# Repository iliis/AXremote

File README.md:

NOTE on AX5043 / AX8052F143 support
===================================

If you need help with an AX5043 based project please contact AxsemSupport@onsemi.com first ;)

AXremote
========

Wireless remote for XBMC and other things.

TODO
====

Software
--------
- use deepsleep for radio instead of powerdown
- put mcu into sleep, disable all timers

Hardware
--------
- add GND and VCC vias to PCB (2.57mm pinheader) for easy current measurement
- use DSWAKE and put chip into deepsleep

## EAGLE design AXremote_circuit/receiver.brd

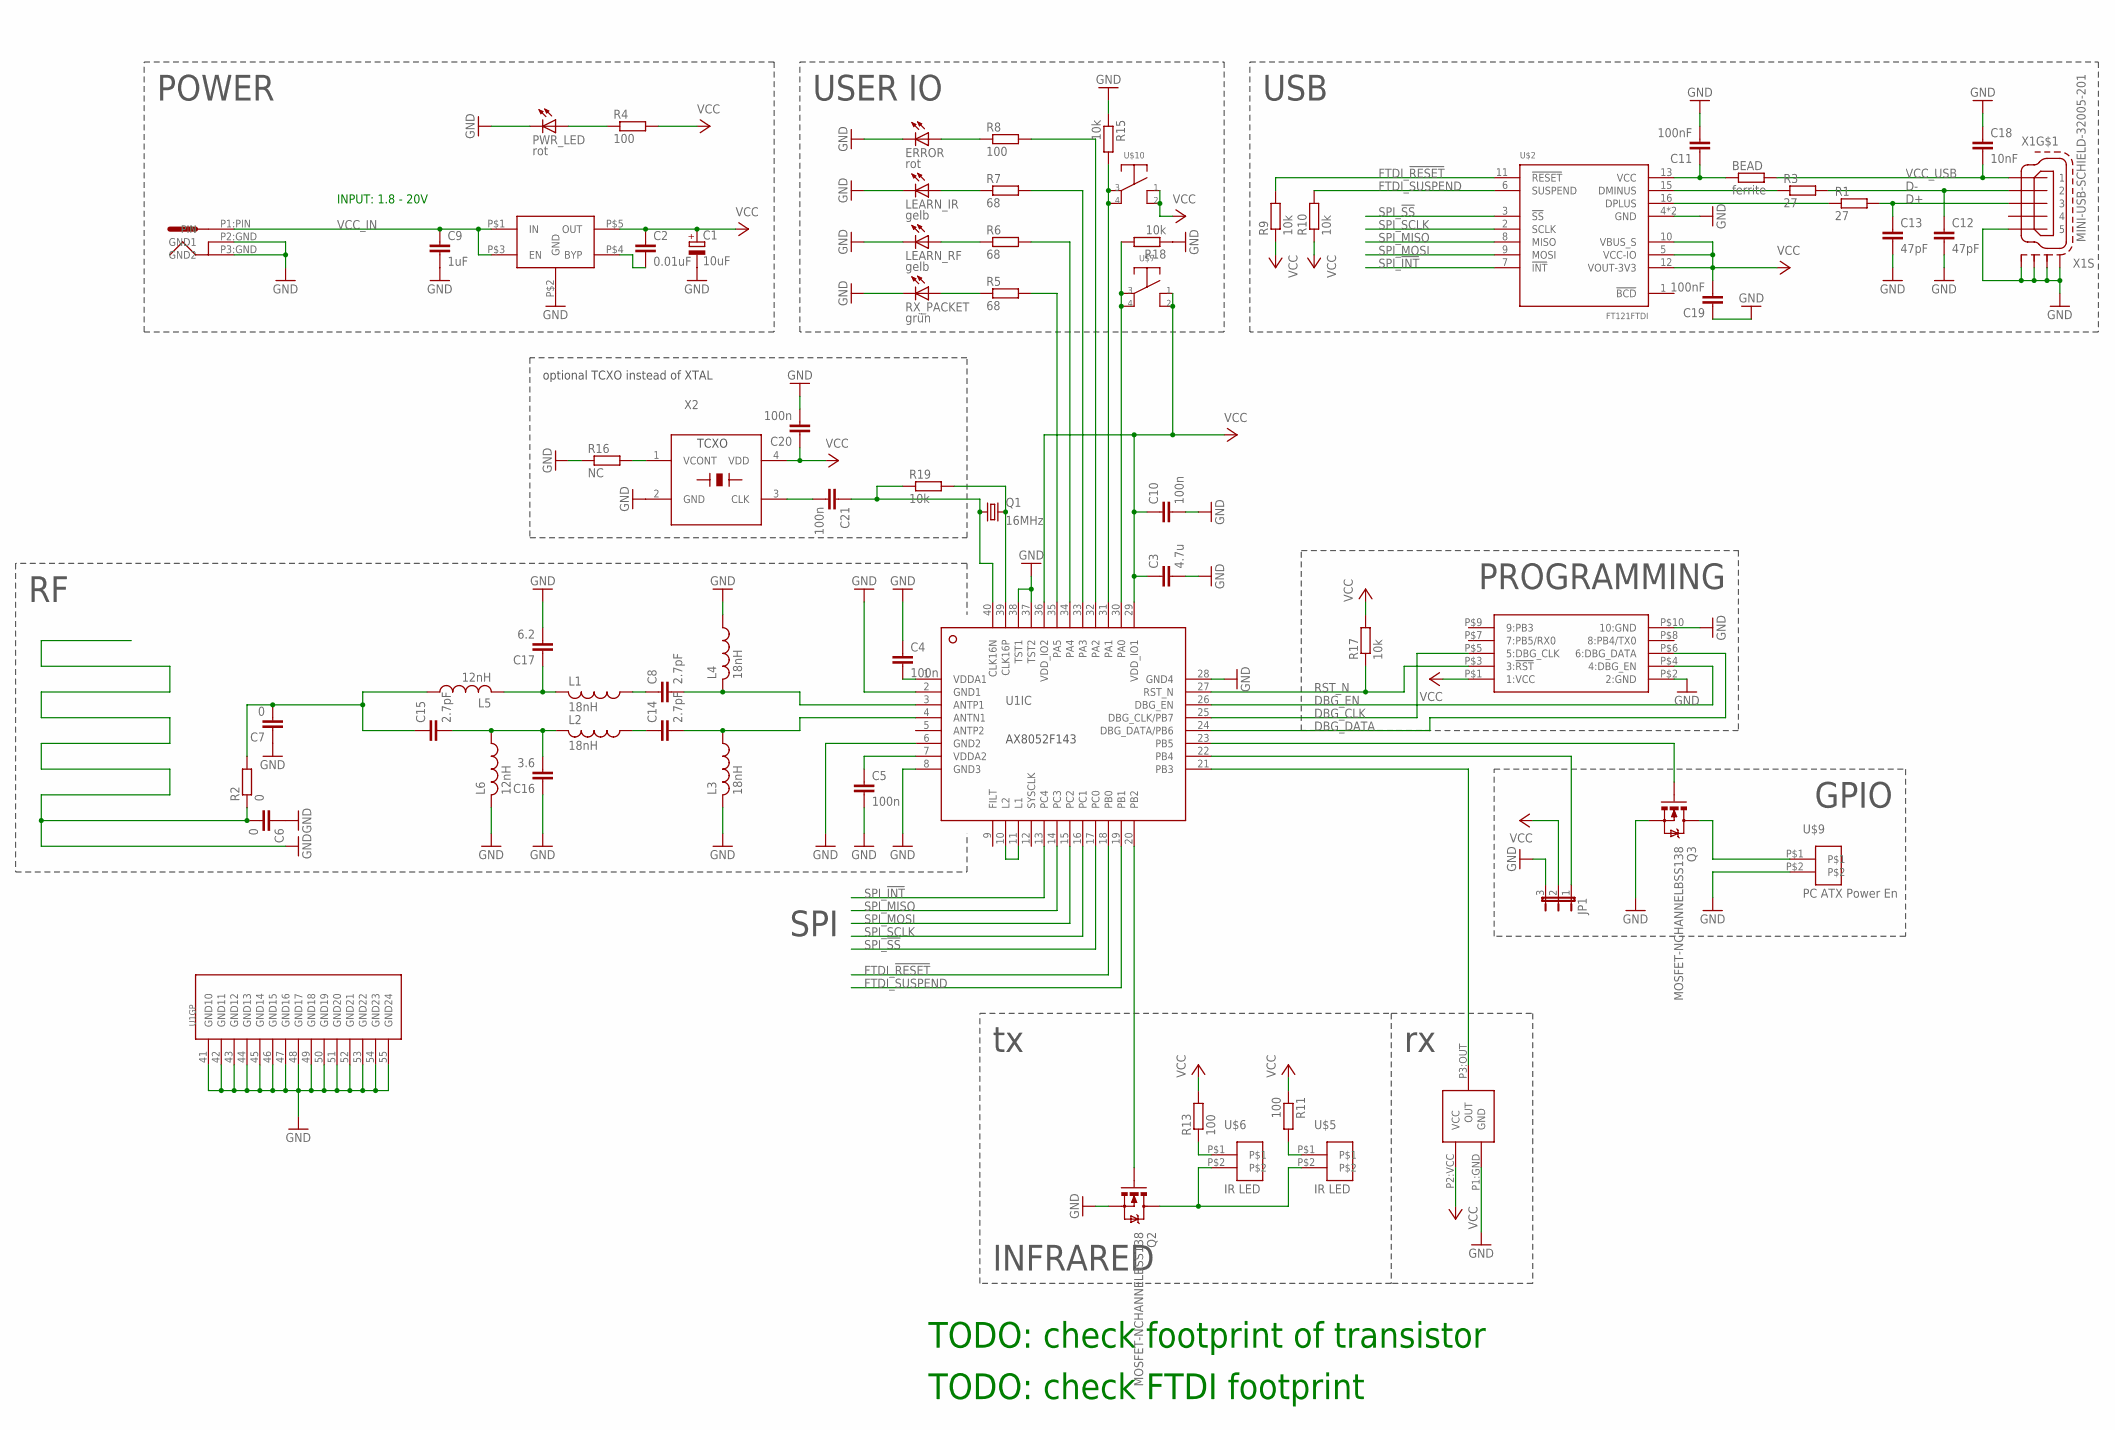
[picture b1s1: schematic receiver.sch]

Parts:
BEAD: ferrite; R0603
C1: 10uF; 153CLV-0405
C2: 0.01uF; C0603
C3: 4.7u; C0805
C4, C5, C10, C20, C21: 100n; C0603
C6, C7: 0; C0603
C8, C14, C15: 2.7pF; C0603
C9: 1uF; C0805K
C11, C19: 100nF; C0603K
C12, C13: 47pF; C0603K
C16: 3.6; C0603
C17: 6.2; C0603
C18: 10nF; C0603K
ERROR: rot; CHIPLED_1206
JP1: JP2E; JP2
L1, L2, L3, L4: 18nH; C0603
L5, L6: 12nH; C0603
LEARN_IR: gelb; CHIPLED_1206
LEARN_RF: gelb; CHIPLED_1206
PWR_LED: rot; CHIPLED_1206
Q1: 16MHz; SM49
Q2, Q3: MOSFET-NCHANNELBSS138; SOT23
R1, R3: 27; R0603
R2: 0; R0603
R4, R8, R11, R13: 100; R0603
R5, R6, R7: 68; R0603
R9, R10, R15, R17, R18, R19: 10k; R0603
R16: NC; R0603
RX_PACKET: grün; CHIPLED_1206
U1: AX8052F143HS; QFN40-H
U$1: LT1761; TSOT-23
U$2: FT121FTDI; TSSOP16-FTDI
U$3: 2X5PIN-CONNECTOR; 2X5PIN-CONNECTOR-SMD
U$4: POWER_JACK; POWER_JACK_3.4/1
U$5, U$6: IR LED; 2PIN_PINHEADER
U$7, U$10: SWITCHSMD; TACTILE_SWITCH_FSM2JSMA
U$8: IR_RECEIVER; TSOP1738_IR_RECV
U$9: PC ATX Power En; 2PIN_PINHEADER
X1: MINI-USB-SCHIELD-32005-201; 32005-201
X2: TCXO3225; X3225

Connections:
D+: C13.1, R1.2, X1.3
D-: C12.1, R3.2, X1.2
DBG_CLK: U1.25 (DBG_CLK/PB7), U$3.P$5 (5:DBG_CLK)
DBG_DATA: U1.24 (DBG_DATA/PB6), U$3.P$6 (6:DBG_DATA)
DBG_EN: U1.26 (DBG_EN), U$3.P$4 (4:DBG_EN)
FTDI_!RESET: R9.2, U1.18 (PB0), U$2.11 (!RESET)
FTDI_SUSPEND: R10.2, U1.19 (PB1), U$2.6 (SUSPEND)
GND: C1.-, C3.2, C4.1, C5.2, C6.1, C6.2, C7.1, C9.2, C10.2, C11.2, C12.2, C13.2, C16.1, C17.2, C18.1, C19.1, C20.2, ERROR.C, JP1.3, L3.2, L4.1, L6.2, LEARN_IR.C, LEARN_RF.C, PWR_LED.C, Q2.2 (S), Q3.2 (S), R2.1, R15.1, R16.1, R18.1, RX_PACKET.C, U1.2 (GND1), U1.6 (GND2), U1.8 (GND3), U1.28 (GND4), U1.37 (TST2), U1.38 (TST1), U1.41 (GND10), U1.42 (GND11), U1.43 (GND12), U1.44 (GND13), U1.45 (GND14), U1.46 (GND15), U1.47 (GND16), U1.48 (GND17), U1.49 (GND18), U1.50 (GND19), U1.51 (GND20), U1.52 (GND21), U1.53 (GND22), U1.54 (GND23), U1.55 (GND24), U$1.P$2 (GND), U$2.4 (GND), U$2.14 (GND), U$3.P$2 (2:GND), U$3.P$10 (10:GND), U$4.P2:GND (GND1), U$4.P3:GND (GND2), U$8.P1:GND (GND), U$9.P$2, X1.5, X1.M1 (S1), X1.M2 (S2), X1.M3 (S3), X1.M4 (S4), X2.2 (GND)
unnamed: U1.10 (L2), U1.11 (L1)
unnamed: R1.1, U$2.16 (DPLUS)
unnamed: C4.2, U1.1 (VDDA1)
unnamed: C2.2, U$1.P$4 (BYP)
unnamed: R3.1, U$2.15 (DMINUS)
unnamed: C5.1, U1.7 (VDDA2)
unnamed: C8.2, L4.2, U1.3 (ANTP1)
unnamed: C14.2, L3.1, U1.4 (ANTN1)
unnamed: C8.1, L1.1
unnamed: C14.1, L2.1
unnamed: BEAD.1, C11.1, U$2.13 (VCC)
unnamed: C17.1, L1.2, L5.2
unnamed: C15.2, C16.2, L2.2, L6.1
unnamed: Q1.2, R19.2, U1.39 (CLK16P)
unnamed: C21.1, Q1.1, R19.1, U1.40 (CLK16N)
unnamed: JP1.1, U1.22 (PB4)
unnamed: R15.2, U1.31 (PA1), U$10.P3, U$10.P4
unnamed: PWR_LED.A, R4.1
unnamed: R16.2, X2.1 (VCONT)
unnamed: C7.2, C15.1, L5.1, R2.2
unnamed: U1.21 (PB3), U$8.P3:OUT (OUT)
unnamed: C21.2, X2.3 (CLK)
unnamed: R5.1, RX_PACKET.A
unnamed: R5.2, U1.35 (PA5)
unnamed: R18.2, U1.30 (PA0), U$7.P3, U$7.P4
unnamed: LEARN_RF.A, R6.1
unnamed: LEARN_IR.A, R7.1
unnamed: ERROR.A, R8.1
unnamed: R6.2, U1.34 (PA4)
unnamed: R7.2, U1.33 (PA3)
unnamed: R8.2, U1.32 (PA2)
unnamed: R11.2, U$5.P$1
unnamed: R13.1, U$6.P$1
unnamed: Q2.3 (D), U$5.P$2, U$6.P$2
unnamed: Q2.1 (G), U1.20 (PB2)
unnamed: Q3.1 (G), U1.23 (PB5)
unnamed: Q3.3 (D), U$9.P$1
RST_N: R17.1, U1.27 (RST_N), U$3.P$3 (3:!RST)
SPI_!INT: U1.13 (PC4), U$2.7 (!INT)
SPI_!SS: U1.17 (PC0), U$2.3 (!SS)
SPI_MISO: U1.14 (PC3), U$2.8 (MISO)
SPI_MOSI: U1.15 (PC2), U$2.9 (MOSI)
SPI_SCLK: U1.16 (PC1), U$2.2 (SCLK)
VCC: C1.+, C2.1, C3.1, C10.1, C19.2, C20.1, JP1.2, R4.2, R9.1, R10.1, R11.1, R13.2, R17.2, U1.29 (VDD_IO1), U1.36 (VDD_IO2), U$1.P$5 (OUT), U$2.5 (VCC-IO), U$2.10 (VBUS_S), U$2.12 (VOUT-3V3), U$3.P$1 (1:VCC), U$7.P1, U$7.P2, U$8.P2:VCC (VCC), U$10.P1, U$10.P2, X2.4 (VDD)
VCC_IN: C9.1, U$1.P$1 (IN), U$1.P$3 (EN), U$4.P1:PIN (PIN)
VCC_USB: BEAD.2, C18.2, X1.1

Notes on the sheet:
INPUT: 1.8 - 20V
TODO: check footprint of transistor
optional TCXO instead of XTAL
POWER
USER IO
USB
INFRARED
GPIO
PROGRAMMING
SPI
TODO: check FTDI footprint

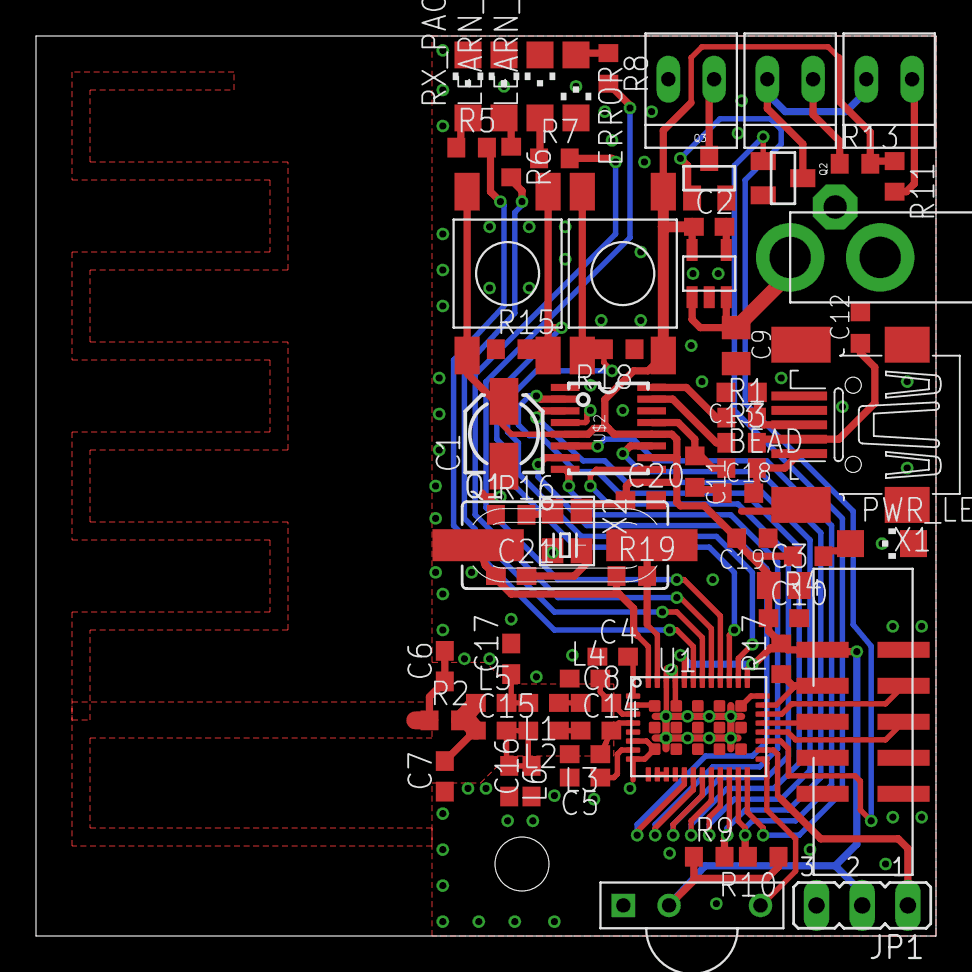
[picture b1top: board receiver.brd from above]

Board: 2 copper layers, 50.0 x 50.0 mm, 68 parts (1 on the bottom side), 54 nets.

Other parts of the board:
U$11: APERTURE_LOGO_BLACK

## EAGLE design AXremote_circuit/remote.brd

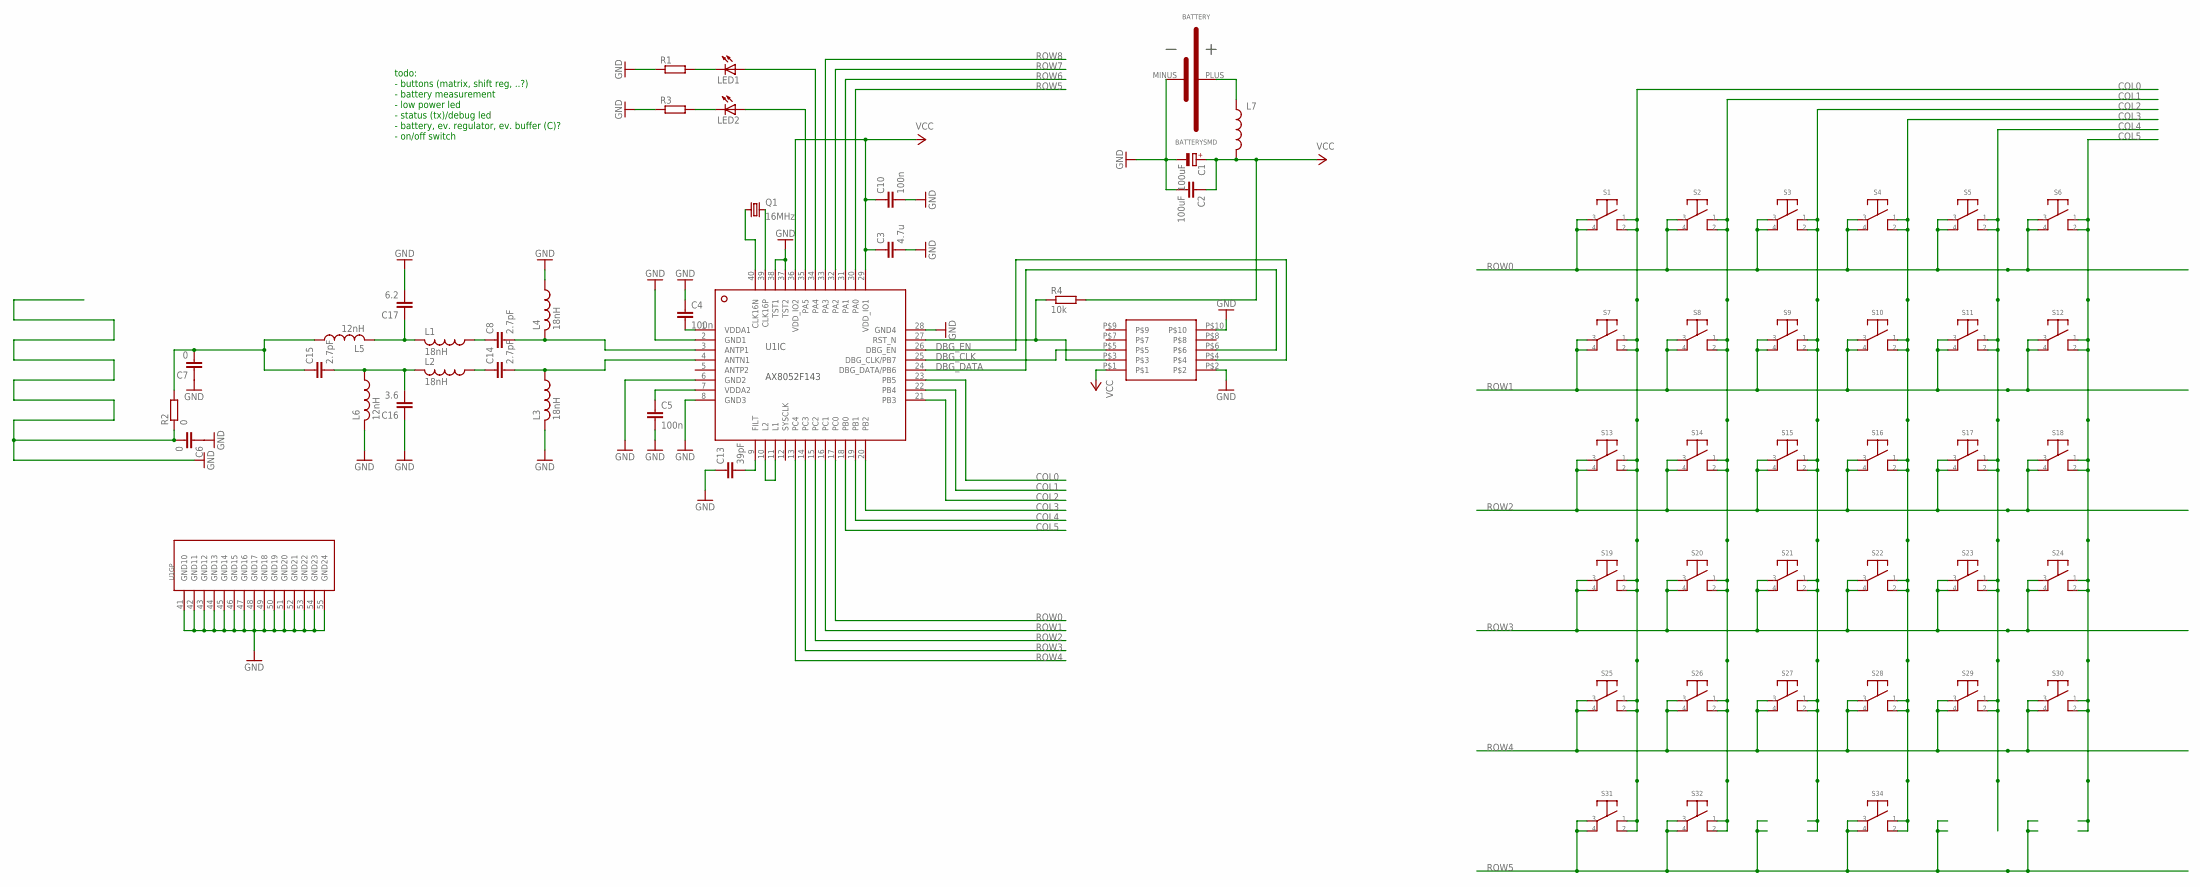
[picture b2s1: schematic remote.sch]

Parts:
BATTERY: BATTERYSMD; CR2032-SMD
C1: 100uF; PANASONIC_E
C2: 100uF; C1206K
C3: 4.7u; C0805
C4, C5, C10: 100n; C0603
C6, C7: 0; C0805
C8, C14, C15: 2.7pF; C0805
C13: 39pF; C0805
C16: 3.6; C0805
C17: 6.2; C0805
L1, L2, L3, L4: 18nH; C0603
L5, L6: 12nH; C0603
L7: INDUCTORNPI75; NPI75C
LED1, LED2: LEDCHIPLED_1206; CHIPLED_1206
Q1: 16MHz; SM49
R1, R3: R-EU_R0603; R0603
R2: 0; R0603
R4: 10k; R0603
S1, S2, S3, S4, S5, S6, S7, S8, S9, S10, S11, S12, S13, S14, S15, S16, S17, S18, S19, S20, S21, S22, S23, S24, S25, S26, S27, S28, S29, S30, S31, S32, S34: SWITCHSMD; TACTILE_SWITCH_FSM2JSMA
U1: AX8052F143HS; QFN40-H
U$2: 2X5PIN-CONNECTOR; 2X5PIN-CONNECTOR-SMD

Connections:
COL0: S1.P1, S1.P2, S7.P1, S7.P2, S13.P1, S13.P2, S19.P1, S19.P2, S25.P1, S25.P2, S31.P1, S31.P2, U1.23 (PB5)
COL1: S2.P1, S2.P2, S8.P1, S8.P2, S14.P1, S14.P2, S20.P1, S20.P2, S26.P1, S26.P2, S32.P1, S32.P2, U1.22 (PB4)
COL2: S3.P1, S3.P2, S9.P1, S9.P2, S15.P1, S15.P2, S21.P1, S21.P2, S27.P1, S27.P2, U1.21 (PB3)
COL3: S4.P1, S4.P2, S10.P1, S10.P2, S16.P1, S16.P2, S22.P1, S22.P2, S28.P1, S28.P2, S34.P1, S34.P2, U1.20 (PB2)
COL4: S5.P1, S5.P2, S11.P1, S11.P2, S17.P1, S17.P2, S23.P1, S23.P2, S29.P1, S29.P2, U1.19 (PB1)
COL5: S6.P1, S6.P2, S12.P1, S12.P2, S18.P1, S18.P2, S24.P1, S24.P2, S30.P1, S30.P2, U1.18 (PB0)
DBG_CLK: U1.25 (DBG_CLK/PB7), U$2.P$5
DBG_DATA: U1.24 (DBG_DATA/PB6), U$2.P$6
DBG_EN: U1.26 (DBG_EN), U$2.P$4
GND: BATTERY.MINUS, C1.-, C2.2, C3.2, C4.1, C5.2, C6.1, C6.2, C7.1, C10.2, C13.1, C16.1, C17.2, L3.2, L4.1, L6.2, R1.1, R2.1, R3.1, U1.2 (GND1), U1.6 (GND2), U1.8 (GND3), U1.28 (GND4), U1.37 (TST2), U1.38 (TST1), U1.41 (GND10), U1.42 (GND11), U1.43 (GND12), U1.44 (GND13), U1.45 (GND14), U1.46 (GND15), U1.47 (GND16), U1.48 (GND17), U1.49 (GND18), U1.50 (GND19), U1.51 (GND20), U1.52 (GND21), U1.53 (GND22), U1.54 (GND23), U1.55 (GND24), U$2.P$2, U$2.P$10
unnamed: U1.10 (L2), U1.11 (L1)
unnamed: C13.2, U1.9 (FILT)
unnamed: C4.2, U1.1 (VDDA1)
unnamed: LED1.A, U1.34 (PA4)
unnamed: R4.1, U1.27 (RST_N), U$2.P$3
unnamed: C5.1, U1.7 (VDDA2)
unnamed: C8.2, L4.2, U1.3 (ANTP1)
unnamed: C14.2, L3.1, U1.4 (ANTN1)
unnamed: C8.1, L1.1
unnamed: C14.1, L2.1
unnamed: LED2.A, U1.35 (PA5)
unnamed: C17.1, L1.2, L5.2
unnamed: C15.2, C16.2, L2.2, L6.1
unnamed: Q1.2, U1.39 (CLK16P)
unnamed: Q1.1, U1.40 (CLK16N)
unnamed: LED2.C, R3.2
unnamed: LED1.C, R1.2
unnamed: BATTERY.PLUS, L7.1
unnamed: C7.2, C15.1, L5.1, R2.2
ROW0: S1.P3, S1.P4, S2.P3, S2.P4, S3.P3, S3.P4, S4.P3, S4.P4, S5.P3, S5.P4, S6.P3, S6.P4, U1.17 (PC0)
ROW1: S7.P3, S7.P4, S8.P3, S8.P4, S9.P3, S9.P4, S10.P3, S10.P4, S11.P3, S11.P4, S12.P3, S12.P4, U1.16 (PC1)
ROW2: S13.P3, S13.P4, S14.P3, S14.P4, S15.P3, S15.P4, S16.P3, S16.P4, S17.P3, S17.P4, S18.P3, S18.P4, U1.15 (PC2)
ROW3: S19.P3, S19.P4, S20.P3, S20.P4, S21.P3, S21.P4, S22.P3, S22.P4, S23.P3, S23.P4, S24.P3, S24.P4, U1.14 (PC3)
ROW4: S25.P3, S25.P4, S26.P3, S26.P4, S27.P3, S27.P4, S28.P3, S28.P4, S29.P3, S29.P4, S30.P3, S30.P4, U1.13 (PC4)
ROW5: S31.P3, S31.P4, S32.P3, S32.P4, S34.P3, S34.P4, U1.30 (PA0)
ROW6: U1.31 (PA1)
ROW7: U1.32 (PA2)
ROW8: U1.33 (PA3)
VCC: C1.+, C2.1, C3.1, C10.1, L7.2, R4.2, U1.29 (VDD_IO1), U1.36 (VDD_IO2), U$2.P$1

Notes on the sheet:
todo: - buttons (matrix, shift reg, ..?) - battery measurement - low power led - status (tx)/debug led - battery, ev. regulator, ev. buffer (C)? - on/off switch

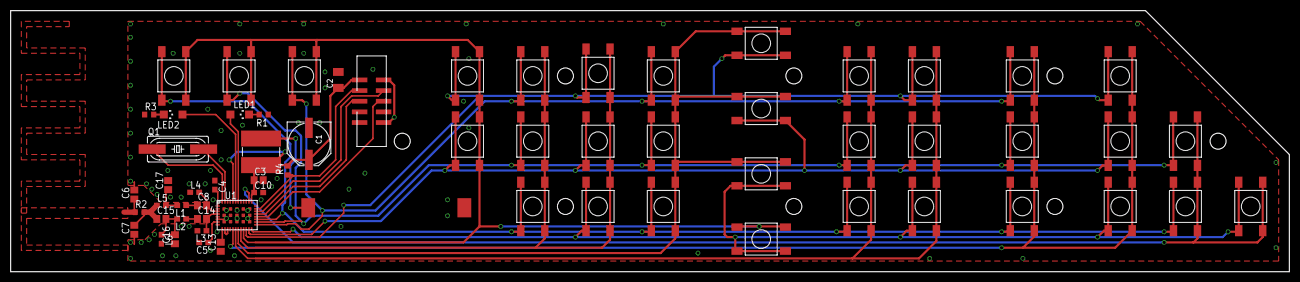
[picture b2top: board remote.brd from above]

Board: 2 copper layers, 240.0 x 49.0 mm, 89 parts (0 on the bottom side), 36 nets.

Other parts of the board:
U$1, U$10, U$11, U$12: ARROW
U$3: PC; POWER_TEXT
U$4: APERTURE_LOGO
U$5: TV; POWER_TEXT
U$6: AUDIO; POWER_TEXT
U$7: HOME
U$9: STOP
U$13, U$14: ARROW_DOUBLE
U$15: ARROW_BACK
U$16: PLAY_PAUSE
U$17, U$18: FAST_FORWARD
U$19, U$20: FAST_FORWARD_NEXT
U$21, U$22, U$23: PLUS
U$24, U$25, U$26: MINUS
U$27: ARROW_ROT_RIGHT

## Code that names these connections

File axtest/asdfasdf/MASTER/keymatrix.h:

#ifndef KEYMATRIX_H_INCLUDED
#define KEYMATRIX_H_INCLUDED

#include <ax8052f143.h>
#include <libmftypes.h>

#include "../COMMON/misc.h"

// Mapping between physical pins on microcontroller
// and logical rows/cols

#define ROW_PORT_0  C
#define ROW_PORT_1  C
#define ROW_PORT_2  C
#define ROW_PORT_3  C
#define ROW_PORT_4  C
#define ROW_PORT_5  A
#define ROW_PORT_6  A
#define ROW_PORT_7  A
#define ROW_PORT_8  A

#define COL_PORT_0  B
#define COL_PORT_1  B
#define COL_PORT_2  B
#define COL_PORT_3  B
#define COL_PORT_4  B
#define COL_PORT_5  B

#define ROW_PIN_0   0
#define ROW_PIN_1   1
#define ROW_PIN_2   2
#define ROW_PIN_3   3
#define ROW_PIN_4   4
#define ROW_PIN_5   0
#define ROW_PIN_6   1
#define ROW_PIN_7   2
#define ROW_PIN_8   3

#define COL_PIN_0   5
#define COL_PIN_1   4
#define COL_PIN_2   3
#define COL_PIN_3   2
#define COL_PIN_4   1
#define COL_PIN_5   0

// duplicated information:

#define ROW0    C_0
#define ROW1    C_1
#define ROW2    C_2
#define ROW3    C_3
#define ROW4    C_4
#define ROW5    A_0
#define ROW6    A_1
#define ROW7    A_2
#define ROW8    A_3

#define COL     B
#define COL0    B_5
#define COL1    B_4
#define COL2    B_3
#define COL3    B_2
#define COL4    B_1
#define COL5    B_0

#define READ_COL()  ((~PINB) & 0x3F)    // 0 == pressed -> invert
#define INIT_COL()  do { \
        /* set as input */ \
        DIRB &= (uint8_t) (~0x3F); \
        /* enable pullup */ \
        PORTB |= 0x3F; \
    } while (0)


// DIR: 0 = input, 1 = output
// PIN: value of pin (read only)
// PORT: if input (DIR == 0): 0 = no pullup, 1 = pullup
//       if output: value of pin

#define ALL_ROWS_Z()    do { \
        /* set to input */ \
        DIRC &= (uint8_t) ~0x1F;    \
        DIRA &= (uint8_t) ~0x0F;    \
        /* disable pull-up */ \
        PORTC &= (uint8_t) ~0x1F;    \
        PORTA &= (uint8_t) ~0x0F;    \
    } while (0)


#define SET_REGISTER_0(reg, port, pin)  do { reg##port &= (uint8_t) (~(1<<(pin))); } while(0)
#define SET_REGISTER_1(reg, port, pin)  do { reg##port |= (uint8_t) ( (1<<(pin))); } while(0)

#define SET_REGISTER(reg, port, pin, value) SET_REGISTER_##value(reg, port, pin)

#define SET_REGISTER_ROW(reg, x, value) SET_REGISTER(reg, ROW_PORT_##x, ROW_PIN_##x, value)
#define SET_REGISTER_COL(reg, x, value) SET_REGISTER(reg, COL_PORT_##x, COL_PIN_##x, value)


#define DRIVE_ROW(x)    do { \
        /* set to output */ \
        SET_REGISTER_ROW(DIR, x, 1); \
        /* output = 0 */ \
        SET_REGISTER_ROW(PORT, x, 0); \
    } while (0)


// "reverse" shift, i.e. discrete log (READ_COL() gives a bitmask, we want a number)
// e.g. "0x04" --> 3
//      "0x10" --> 5

#define DISC_LOG(x)     ( x & 0x80 ? 8 :    \
                        ( x & 0x40 ? 7 :    \
                        ( x & 0x20 ? 6 :    \
                        ( x & 0x10 ? 5 :    \
                        ( x & 0x08 ? 4 :    \
                        ( x & 0x04 ? 3 :    \
                        ( x & 0x02 ? 2 :    \
                        ( x & 0x01 ? 1 : 0))))))))

// X-Macro for "looping" over rows
#define FOR_0_TO_5  \
    F(0)    \
    F(1)    \
    F(2)    \
    F(3)    \
    F(4)    \
    F(5)

uint8_t scan_keymatrix();

#endif // KEYMATRIX_H_INCLUDED

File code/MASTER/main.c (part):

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#ifdef DVK2B
    PORTA = 0xC0 | (0x25); 	// pull-up for PA[6,7] which are not bonded, no pull up for PA[3,4] (LPXOSC). Output 0 in PA[0,1,2,5] to prevent current consumption in all DIP switch states
    PORTB = 0xFE; //PB[0,1]  (LCD RS, LCD RST) are overwritten by lcd2_portinit(), enable pull-ups for PB[2..7]  (PB[2,3] for buttons, PB[4..7] unused)
    PORTC = 0xF3 | (0x08); 	// set PC0 = 1 (LCD SEL), PC1 = 1 (LCD SCK), PC2 = 0 (LCD MOSI), PC3 =0 (LED), enable pull-ups for PC[4..7] which are not bonded Mind: PORTC[0:1] is set to 0x3 by lcd2_portinit()
    PORTR = 0xCB; // overwritten by ax5043_reset, ax5043_comminit()


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    DIRR = 0x15; // overwritten by ax5043_reset, ax5043_comminit()
#elif defined(AXREMOTE_TRANSMITTER)

    PORTA = 0xFE; // pull-up for PA[6,7] which are not bonded, Output 0 in PA0, pull-up PA[1..3] (unused rows)
    PORTB = 0xFF; // pull-ups on everything
    PORTC = 0xE0; // output 0 on rows, pull-ups for not-bonded outputs (PA[5..7])
    PORTR = 0x0B; // overwritten by ax5043_reset, ax5043_comminit()

    DIRA = 0x31; // PA[0] is output (row5), PA[1..3] is inputs (unused rows), PA4 and 5 are LEDs, PA[6..7] are not bonded
    DIRB = 0x00; // PB[0..5] are inputs (cols), B6 and 7 are debug connections (inputs as well)
    DIRC = 0x1F; // PC[0..4] are outputs (rows), PC[5..7] are inputs (not bonded).
    DIRR = 0x15; // overwritten by ax5043_reset, ax5043_comminit()

#elif defined(AXREMOTE_RECEIVER)

    PORTA = 0xC0 | (0x3C); // pull-up for PA[6,7] which are not bonded, Output 0 in PA2, A0 and A1 (button) floating (has external pull-down)
    PORTB = 0xF8; // pull-ups on everything
    PORTC = 0xE0; // output 0 on rows, pull-ups for not-bonded outputs (PA[5..7])
    PORTR = 0xCB; // overwritten by ax5043_reset, ax5043_comminit()

    DIRA = 0x3C; // PA0 and PA1 are inputs (buttons), PA[2..5] are LEDs
    // TODO: these outputs have changed a bit (B4 and B5 are outputs too)
    DIRB = 0x07; // PB[0..2] are outputs (IR LEDs etc.), B3 is IR receiver (input), B[4..7] are debug connections (inputs) and UART
    DIRC = 0x03; // PC[0..1] are outputs (IR LEDs), PC[2..7] are inputs (not bonded / connected).
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
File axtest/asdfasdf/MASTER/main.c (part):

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    PORTA = 0xC0 | (PINA & 0x25); 	// pull-up for PA[6,7] which are not bonded, no pull up for PA[3,4] (LPXOSC). Output 0 in PA[0,1,2,5] to prevent current consumption in all DIP switch states
    // init LEDs to previous (frozen) state
    PORTB = 0xFE; //PB[0,1]  (LCD RS, LCD RST) are overwritten by lcd2_portinit(), enable pull-ups for PB[2..7]  (PB[2,3] for buttons, PB[4..7] unused)
    PORTC = 0xF3 | (PINC & 0x08); 	// set PC0 = 1 (LCD SEL), PC1 = 1 (LCD SCK), PC2 = 0 (LCD MOSI), PC3 =0 (LED), enable pull-ups for PC[4..7] which are not bonded Mind: PORTC[0:1] is set to 0x3 by lcd2_portinit()
    // init LEDs to previous (frozen) state
    PORTR = 0xCB; // overwritten by ax5043_reset, ax5043_comminit()

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    PORTR = 0xCB; //

    DIRA = 0x00; //
    DIRB = 0x06; //  PB1 = LED, PB2 = TCXO ON/OFF
    DIRC = 0x00; //  PC4 = button
    DIRR = 0x15; //
    PALTRADIO |= (1<<6);
#endif // else MINI_KIT
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
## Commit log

2013-11-19 Inital schematics.
2013-11-20 Add application note DN023 from TI for antenna.
2013-11-20 Change schematics to single-ended.
    Warning: Commit contains temporary files.
2013-11-20 Simplified schematics (only one crystal).
2013-11-23 Layouted board with antenna.
2013-11-23 Render schematics and board to PDF.
2013-11-25 Moved antenna components closer to chip, better ground connection[s].
    According to Thomas' tips.
2013-11-28 Add production files.
2013-12-05 Add solder mask.
2013-12-21 Add libs.
2013-12-21 Add working code!
    Yeeehaaaaa!
2013-12-21 Fix progconnector in schematic. Add TODOs.
2013-12-23 remote almost complete
2013-12-24 Remote and receiver done.
2014-02-13 Update code to working copy from Bastli-NAS.
2014-02-13 Rename code to something more sensible.
2014-02-13 Fix delay_ms() bug, keymatrix functional.
2014-02-13 Fix some glitching, send packet.
    Still not perfectly happy with keymatrix, an improbably long delay is
    necessary to eliminate glitches.
2014-02-14 Start implementing receiver.
2014-02-14 RX works! Update axradiolab1state.xml.
    Something seemed to be wrong with config_16MHz.c
2014-02-14 Add basic code for AVR (usb).
2014-02-19 Fix some small project bugs in receiver code.
2014-04-21 add a few keys
2014-04-21 usb works (cold solder joint!)
2014-05-10 First ugly table generator for USB keys.
2014-05-10 Cleanup and use keycode list.
2014-05-11 Added a few keys.
2014-05-11 Move key_table to separate file.
2014-05-11 Receive and parse Samsung IR messages.
2014-05-17 Fix parsing. Implement tx of Samsung IR.
2014-05-26 Start rev 3, full SMD.
2014-06-09 Routed rev4, all SMD.
2014-06-14 Add labels, holes and decoration.
    Should be ready for production now.
2014-06-15 Export for production.
2014-06-22 Rewrote IR code. Not tested!
2014-06-22 Add YCM config file.
2014-06-22 Implement Sony and Philips RC5 protocols. UNTESTED
2014-06-25 Add TODO for remove circuit/board after first PCB.
    Board rev4 has some minor issues.
2014-06-25 GND polygon thicker, fix typo.
    - 'pc' -> 'PC'
    - ground plane had a width of 0.1 => ground pads had only very thin
    connections to ground plane
2014-06-25 Start work on receiver rev2.
2014-06-27 Replace AVR with FT121 on receiver. Other details.
    - Clean up schematics
    - Use every pin of F143 (second button, GPIO)
    - add TXCO and XTAL
2014-06-29 Started routing receiver rev2.
2014-06-30 Routed receiver rev2.
2014-06-30 Add Aperture Logo to receiver.
2014-07-05 Receiver: Minor fix, export for production.
2014-07-09 Update easyax code, still uses 0.5mA :(
2014-07-10 Set to XTAL instead of TCXO.
2014-07-15 Forgot to add config.c
2014-07-25 Reset chip on error (in release builds)
2014-08-06 add TODOs to readme
2014-08-06 add DVK2b target, use deepsleep for radio
2014-08-09 WIP on powersaving on Transmitter.
2014-08-09 create config.c with good AXRadioLab.
2014-08-09 use 0dBm TX power
2014-08-09 ...
    ARGH argh argh!
2014-08-12 Increase power to XTAL (AX5043_F10).
2014-08-12 WIP on getting the remote to work. DON'T USE
    This commit does NOT contain working code.
    XTAL should be fixed tough (route more power to it with AX5043_F10).
2014-09-26 Add .layout and .depend files to gitignore.
2014-11-03 Add GPIO interrupt handler for receiver buttons.
2014-11-04 Working SPI communication with FTDI chip.
2014-11-04 Start work on actual USB stuff.
    We receive the setup packet, but don't handle it.
2014-11-04 Add appnotes from FTDI on how to use a FT12x.
2014-11-05 WIP on USB.
2014-11-05 working on IR
2014-11-05 Remove SLAVE and TEST as they are not needed.
2014-11-05 Working reception of NEC IR data.
    Has this mess ever worked before? There were some idiotic bugs!
    Add plotting script.
2014-11-05 Plot a bit of SPACE before actual data to give a more intuitive visualization.
2014-11-05 Parsing of NEC codes works quite reliably. The first time.
    Somehow, the repeat codes cause bugs :(
2014-11-05 Implement most of the original IR commands.
2014-11-05 Add remote keycode overview.
2014-11-06 Moved IR RX interrupt handler back into real IRQ.
2014-11-06 updated RL code to 2.4f, tx still buggy
2016-09-20 Add note about AXSEM support to readme

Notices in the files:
axtest/asdfasdf/MASTER/main.c:
Copyright (c) 2007,2008,2009,2010,2011,2012,2013 AXSEM AG
All rights reserved.
parts and their libraries:
SparkFun-DiscreteSemi: Licensing: CC v3.0 Share-Alike You are welcome to use this library for commercial purposes.
